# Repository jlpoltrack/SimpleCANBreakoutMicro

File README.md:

# SimpleCANBreakoutMicro

A tiny CAN transceiver breakout. It converts a microcontroller's logic-level CAN TX/RX to a CAN bus on a JST-GH connector, with an onboard 3.3 V regulator and optional 120 Ω termination.

Designed in KiCad 10. See [SimpleCANBreakout](https://github.com/jlpoltrack/SimpleCANBreakout) for a larger version with solder pads and an AMS1117 regulator.

## Features

- SN65HVD230 3.3 V CAN transceiver, wired for high-speed mode (up to 1 Mbps)
- XC6206 3.3 V LDO, so the board runs from a single 5 V supply
- 120 Ω termination resistor, enabled by a solder jumper (open by default)
- Parts on the top side only

## Connectors

**J1 — MCU side** (1×4 pin header, 2.54 mm)

| Pin | Signal |
|-----|--------|
| 1   | CAN RX |
| 2   | CAN TX |
| 3   | +5V    |
| 4   | GND    |

**J2 — CAN bus** (JST-GH 4-pin, SM04B-GHS-TB)

| Pin | Signal |
|-----|--------|
| 1   | +5V    |
| 2   | CANH   |
| 3   | CANL   |
| 4   | GND    |

The +5V pins on J1 and J2 are connected, so the board can be powered from either side. CAN TX/RX are 3.3 V logic.

## Termination

Bridge **JP1** (bottom side) to connect the 120 Ω resistor across CANH/CANL. Do this only if the board sits at an end of the bus.

## Bill of materials

| Ref        | Value      | Package            | LCSC    |
|------------|------------|--------------------|---------|
| U3         | SN65HVD230 | SOIC-8             | C12084  |
| U2         | XC6206 3.3 V | SOT-23-3         | C5446   |
| C1, C4, C5 | 1 µF       | 0603               |         |
| C2, C3, C6 | 100 nF     | 0603               |         |
| R1         | 120 Ω      | 0603               |         |
| J1         | 1×4 header | 2.54 mm            |         |
| J2         | JST-GH 4-pin | SM04B-GHS-TB     | C189895 |

## Files

- `SimpleCANBreakoutMicro.kicad_sch` / `.kicad_pcb` / `.kicad_pro` — KiCad project
- `SimpleCANBreakoutMicro.pdf` — schematic
- `production/` — fabrication outputs generated with the [Fabrication Toolkit](https://github.com/bennymeg/Fabrication-Toolkit) plugin: Gerbers and drill files (`SimpleCANBreakoutMicro.zip`), BOM, and pick-and-place positions, ready for JLCPCB

## License

[MIT](LICENSE)

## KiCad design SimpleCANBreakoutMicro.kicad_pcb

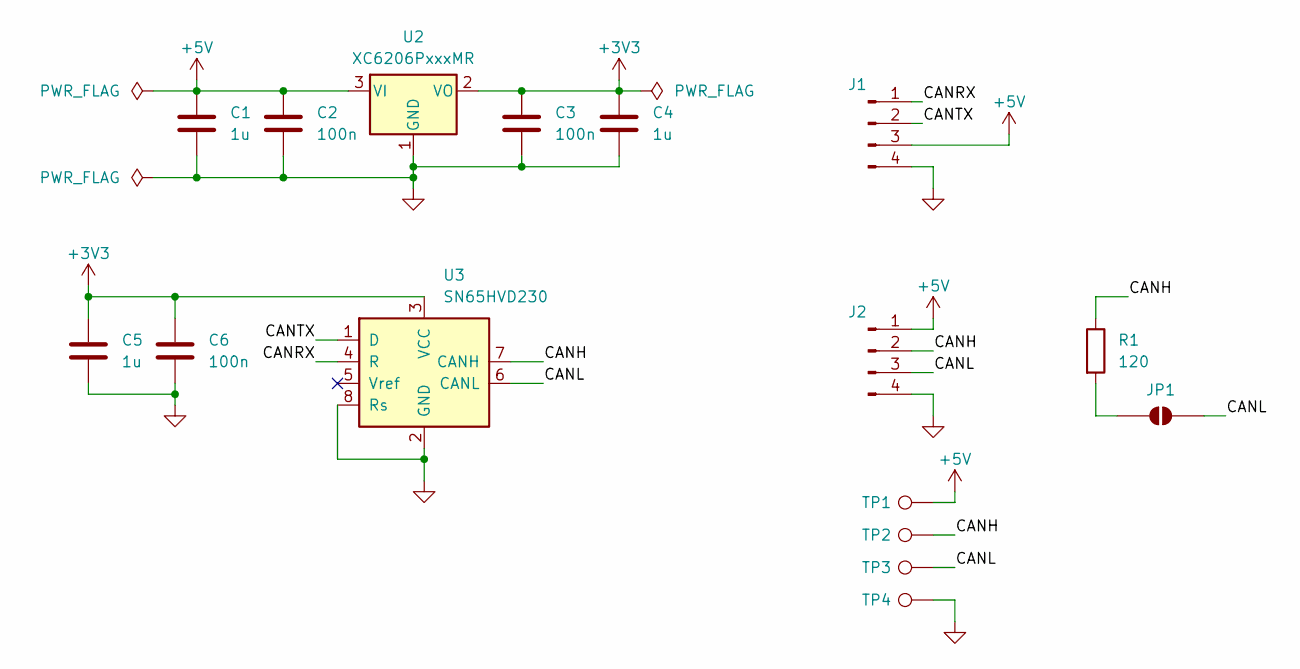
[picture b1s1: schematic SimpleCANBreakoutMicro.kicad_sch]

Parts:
C1, C4, C5: 1u; C_0603_1608Metric
C2, C3, C6: 100n; C_0603_1608Metric
J1: Conn_01x04_Pin; PinHeader_1x04_P2.54mm_Vertical
J2: Conn_01x04_Pin; JST_GH_SM04B-GHS-TB_04x1.25mm_Angled; LCSC Part C189895
JP1: SolderJumper_2_Open; SolderJumper-2_P1.3mm_Open_RoundedPad1.0x1.5mm
R1: 120; R_0603_1608Metric
TP1, TP2, TP3, TP4: TestPoint; TestPoint_Pad_1.0x1.0mm
U2: XC6206PxxxMR; SOT-23-3; LCSC Part C5446
U3: SN65HVD230; SOIC-8_3.9x4.9mm_P1.27mm; LCSC Part C12084

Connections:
+3V3: C3.1, C4.1, C5.1, C6.1, U2.2 (VO), U3.3 (VCC)
+5V: C1.1, C2.1, J1.3, J2.1, TP1.1 (1_1), U2.3 (VI)
/CANH: J2.2, R1.1, TP2.1 (1_1), U3.7 (CANH)
/CANL: J2.3, JP1.2 (B), TP3.1 (1_1), U3.6 (CANL)
/CANRX: J1.1, U3.4 (R)
/CANTX: J1.2, U3.1 (D)
GND: C1.2, C2.2, C3.2, C4.2, C5.2, C6.2, J1.4, J2.4, TP4.1 (1_1), U2.1 (GND), U3.2 (GND), U3.8 (Rs)
unnamed: JP1.1 (A), R1.2

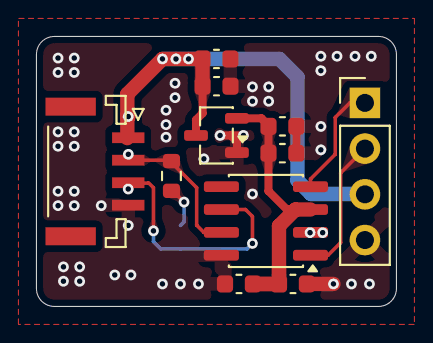
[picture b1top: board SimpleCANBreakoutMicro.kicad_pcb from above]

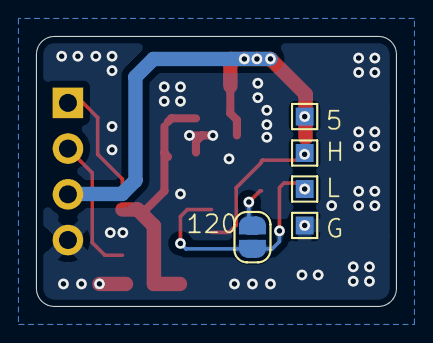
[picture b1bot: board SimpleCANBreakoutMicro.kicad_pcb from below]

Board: 2 copper layers, 20.0 x 15.0 mm, 16 parts (5 on the bottom side), 8 nets.

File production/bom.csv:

Designator,Footprint,Quantity,Value,LCSC Part #
"C1, C4, C5",0603,3,1u,
"C2, C3, C6",0603,3,100n,
J1,PinHeader_1x04_P2.54mm_Vertical,1,Conn_01x04_Pin,
J2,JST_GH_SM04B-GHS-TB_04x1.25mm_Angled,1,Conn_01x04_Pin,C189895
R1,0603,1,120,
U2,SOT-23-3,1,XC6206PxxxMR,C5446
U3,SOIC-8_3.9x4.9mm_P1.27mm,1,SN65HVD230,C12084
